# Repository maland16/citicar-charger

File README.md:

# Citicar Charger
More info to come
This repo is for a controller for the charger on my 1976 Citicar. [Read more about it here.](http://www.devinmalanaphy.com/citicar/)

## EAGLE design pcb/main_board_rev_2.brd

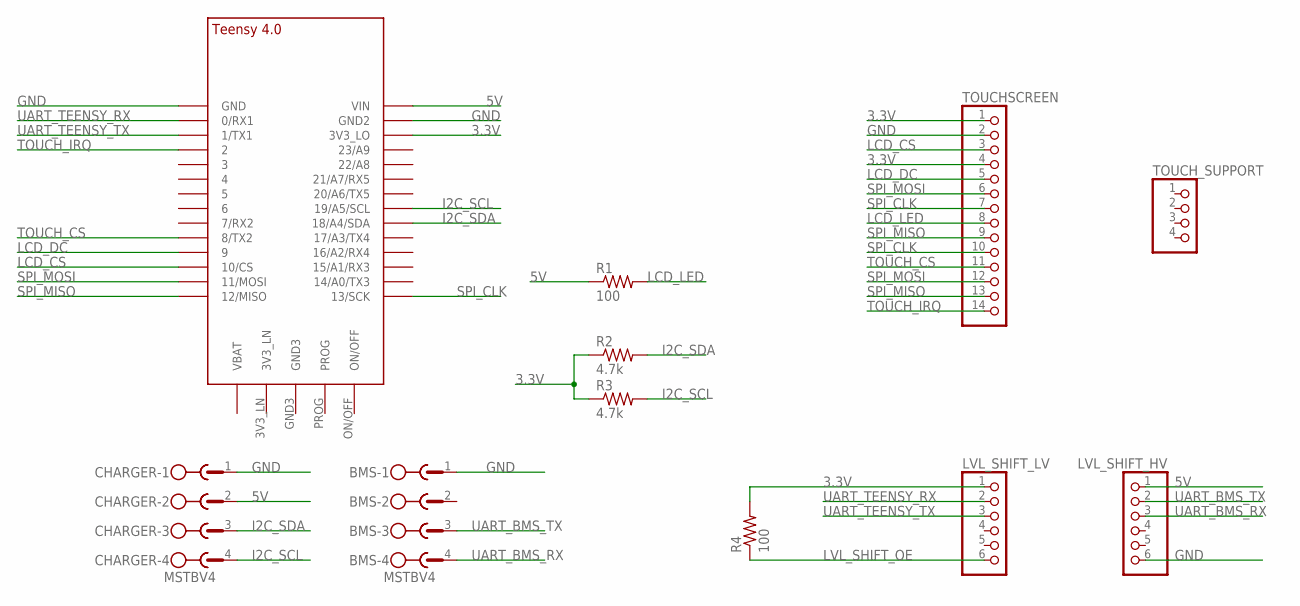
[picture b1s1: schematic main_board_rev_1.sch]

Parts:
BMS: MSTBV4
CHARGER: MSTBV4
LVL_SHIFT_HV: PINHD-1X6; 1X06
LVL_SHIFT_LV: PINHD-1X6; 1X06
R1, R4: 100; 0204/7
R2, R3: 4.7k; 0204/7
TOUCHSCREEN: PINHD-1X14; 1X14
TOUCH_SUPPORT: PINHD-1X4; 1X04
U$1: TEENSY_4.0-BASIC

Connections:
3.3V: LVL_SHIFT_LV.1, R2.1, R3.1, R4.2, TOUCHSCREEN.1, TOUCHSCREEN.4, U$1.3V3_LO
5V: CHARGER.2, LVL_SHIFT_HV.1, R1.1, U$1.VIN
GND: BMS.1, CHARGER.1, LVL_SHIFT_HV.6, TOUCHSCREEN.2, U$1.GND, U$1.GND2
I2C_SCL: CHARGER.4, R3.2, U$1.19/A5/SCL
I2C_SDA: CHARGER.3, R2.2, U$1.18/A4/SDA
LCD_CS: TOUCHSCREEN.3, U$1.10/CS
LCD_DC: TOUCHSCREEN.5, U$1.9/CS (9)
LCD_LED: R1.2, TOUCHSCREEN.8
LVL_SHIFT_OE: LVL_SHIFT_LV.6, R4.1
SPI_CLK: TOUCHSCREEN.7, TOUCHSCREEN.10, U$1.13/SCK
SPI_MISO: TOUCHSCREEN.9, TOUCHSCREEN.13, U$1.12/MISO
SPI_MOSI: TOUCHSCREEN.6, TOUCHSCREEN.12, U$1.11/MOSI
TOUCH_CS: TOUCHSCREEN.11, U$1.8 (8/TX2)
TOUCH_IRQ: TOUCHSCREEN.14, U$1.2
UART_BMS_RX: BMS.4, LVL_SHIFT_HV.3
UART_BMS_TX: BMS.3, LVL_SHIFT_HV.2
UART_TEENSY_RX: LVL_SHIFT_LV.2, U$1.0/RX (0/RX1)
UART_TEENSY_TX: LVL_SHIFT_LV.3, U$1.1/TX (1/TX1)

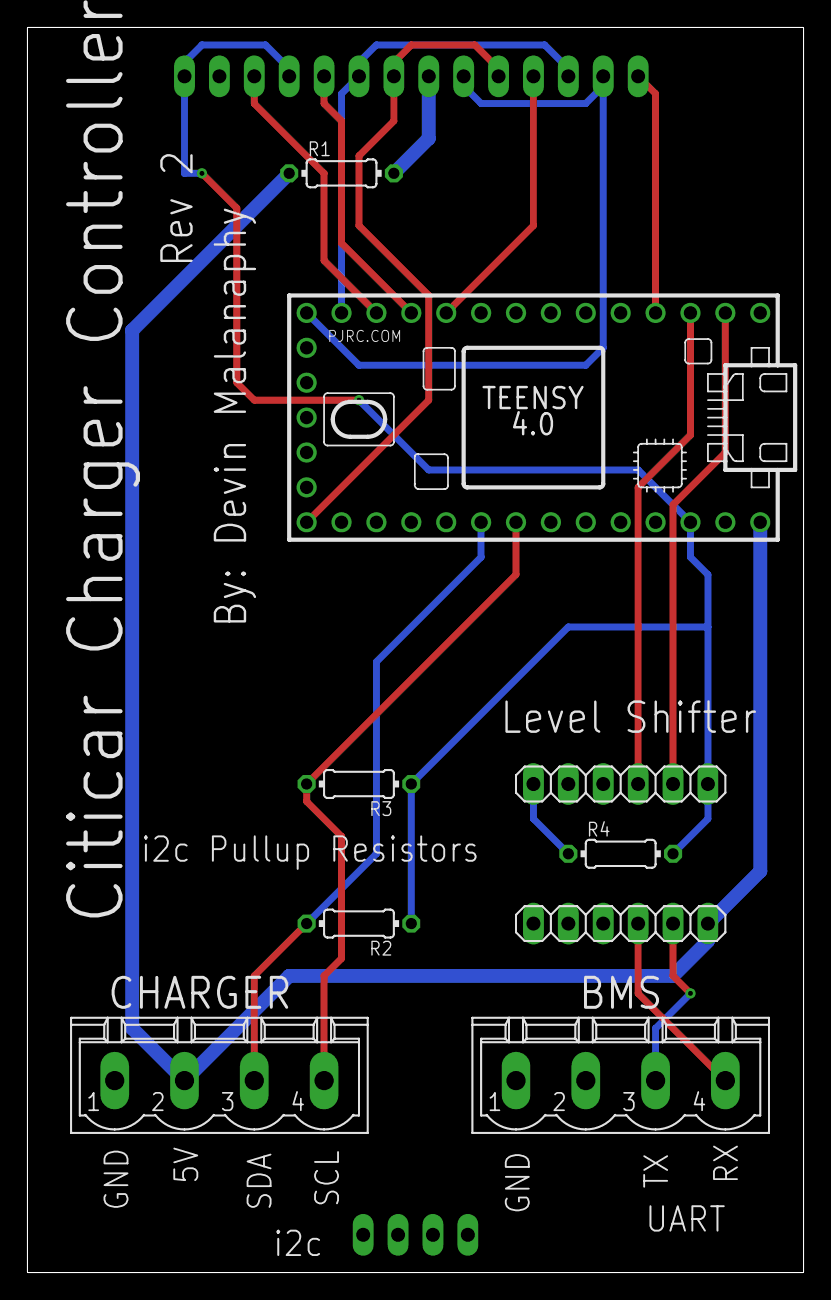
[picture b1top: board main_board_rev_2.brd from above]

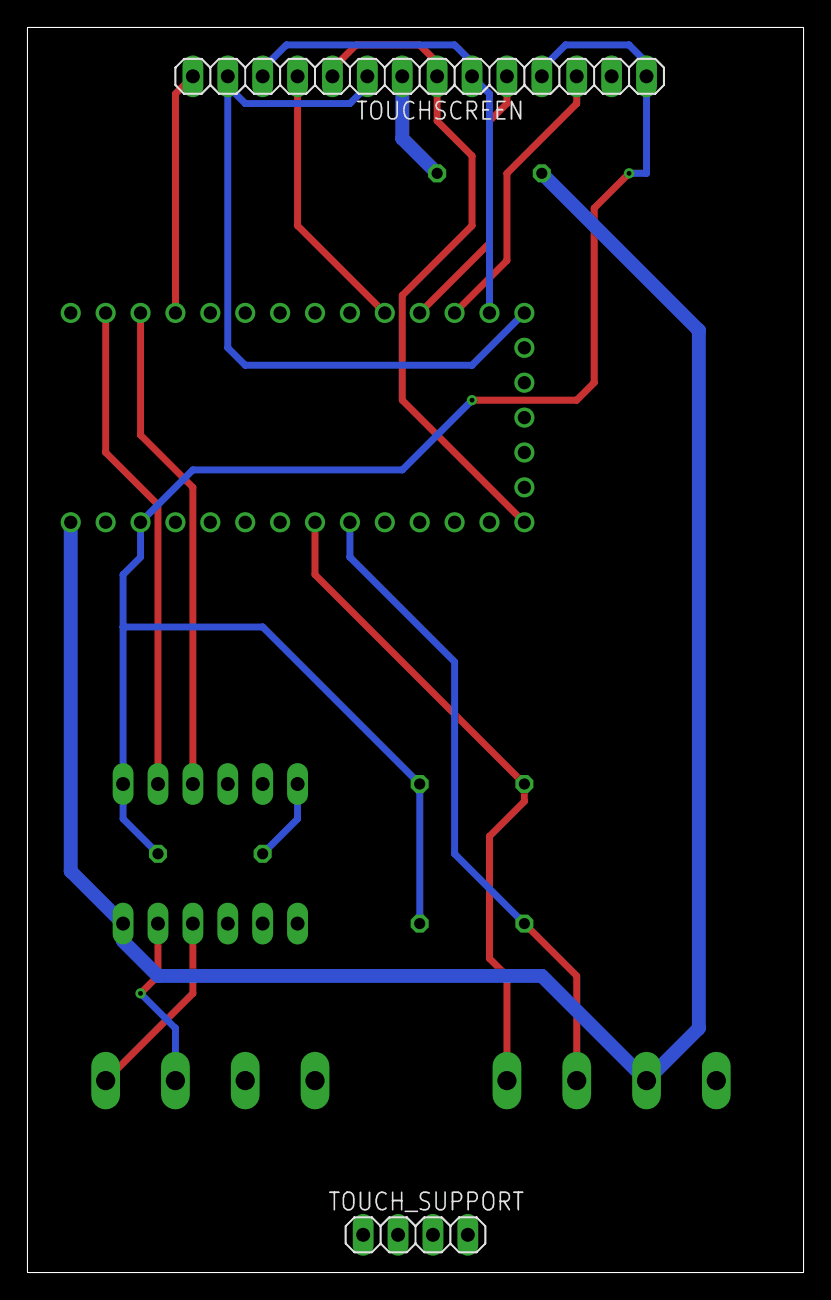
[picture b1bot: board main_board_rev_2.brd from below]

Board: 2 copper layers, 56.5 x 90.6 mm, 11 parts (2 on the bottom side), 18 nets.

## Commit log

2021-06-04 Base implementation, still needs work to get it up and running. No display stuff yet
2021-08-08 Made it look nice, added printout for charger & battery, plus dev modes
2021-09-10 Added all PCB files
2021-09-10 Beginning to implement touch buttons
2021-09-10 charging settings screen created, buttons work. This commit is a fun demo mode
2021-09-10 Added some readme
2021-09-17 Added more logic for configuring charger
2021-10-17 patched compilation issues
2022-04-26 corrected charging speed logic
